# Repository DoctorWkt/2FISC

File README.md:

# FISC2: A TTL CPU with Some 16-bit Capabilities

FISC2 is a microseqenced CPU built from discrete TTL-level components.
It provides
 + recursive **F**unctions,
 + **I**ndexed addressing,
 + **S**tack operations, and
 + some instructions on 16-bit data values

as well as the usual load/store and arithmetic operations, comparisons,
branches and jumps.

The design uses 29 chips and has 8K of ROM, 336K of available RAM and a UART.

## Documentation

The overall design of the CPU is covered in
[Docs/arch_overview.md](Docs/arch_overview.md), and some details
of the hardware implementation are in 
[Docs/fisc2_implementation.md](Docs/fisc2_implementation.md).

## Implementation

At present, I have:

 + a Perl CPU simulator, [csim](csim)
 + an assembler, [cas](cas)
 + a simple compiler, [clc](clc)
 + example assembly and higher-level programs in [Examples](Examples)
 + a Verilog design in [Verilog](Verilog)
 + a final schematic in [Kicad/schematic.pdf](Kicad/schematic.pdf)

## Status of the CPU

**early-July, 2020**: Both the Perl simulator and the Verilog model work
well. I am happy with the design and I've ordered the PCBs and components.

For more detail on progress, you can read my [journal](Docs/journal.md).

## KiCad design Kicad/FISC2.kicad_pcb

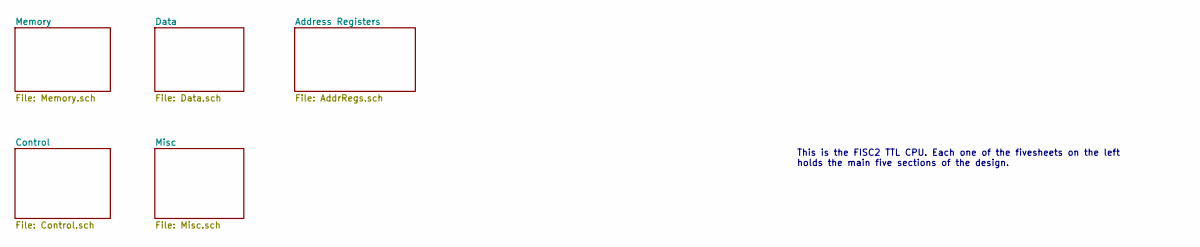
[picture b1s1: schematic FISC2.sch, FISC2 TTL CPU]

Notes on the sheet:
This is the FISC2 TTL CPU. Each one of the fivesheets on the left holds the main five sections of the design.

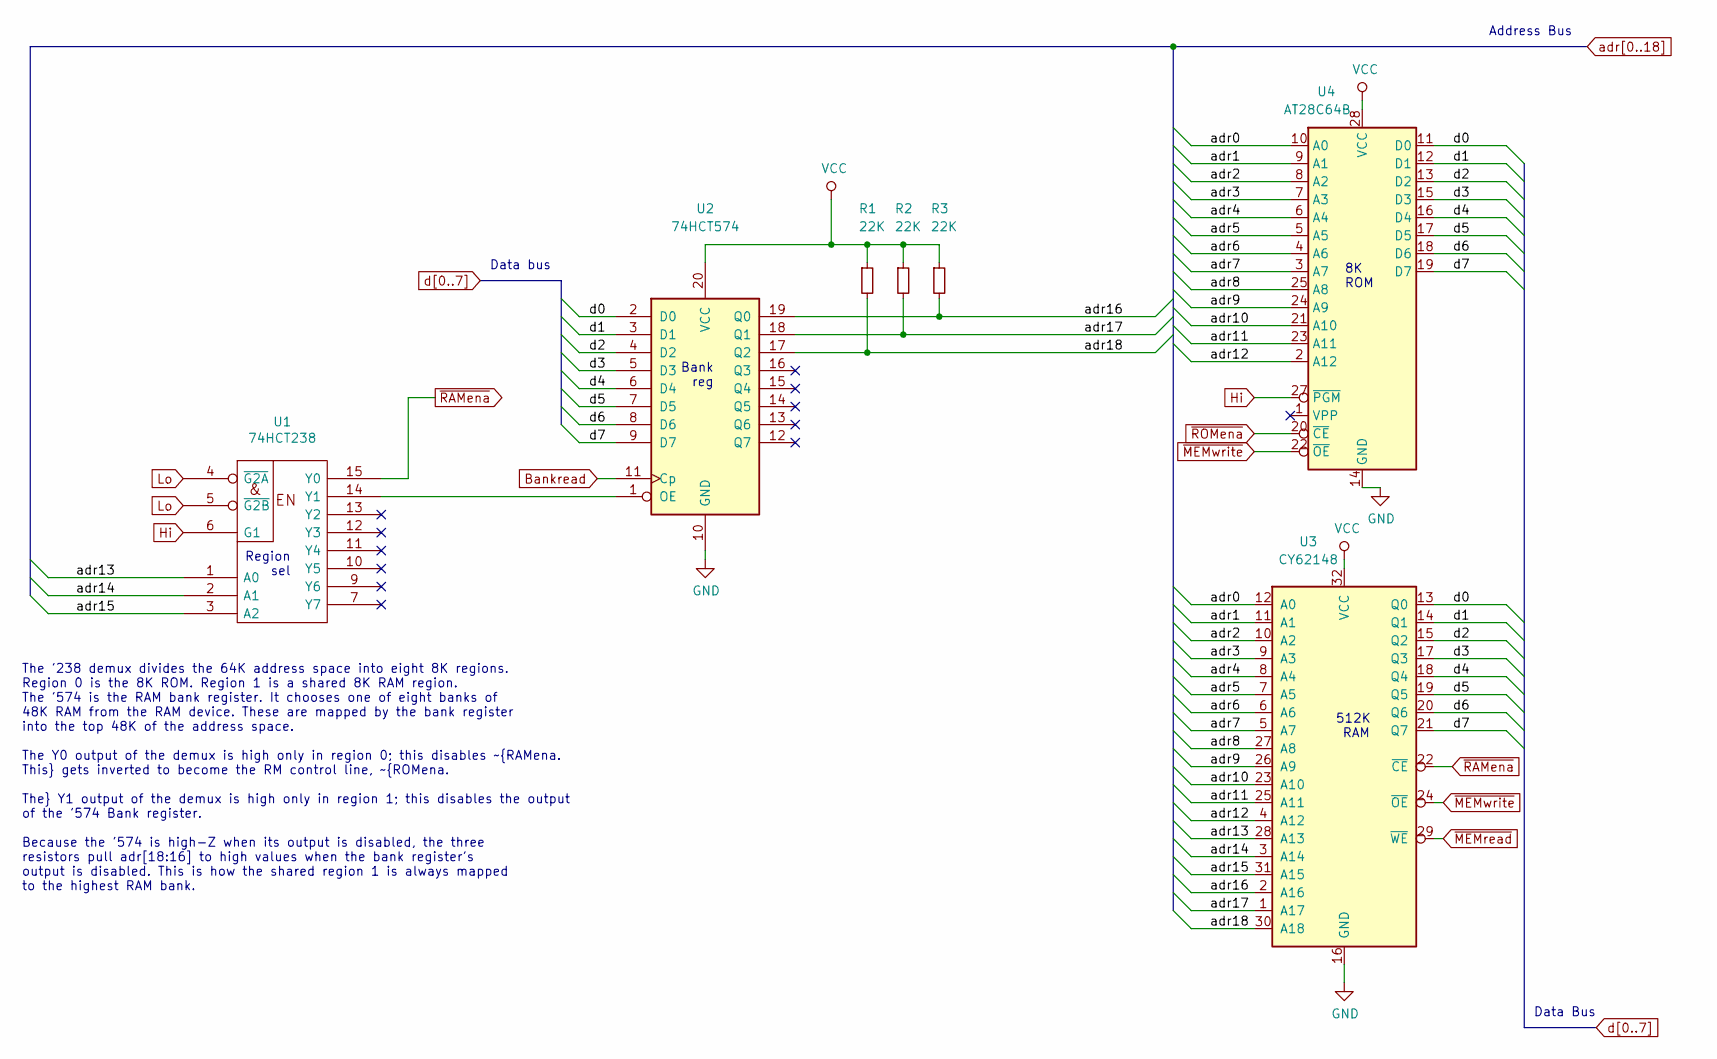
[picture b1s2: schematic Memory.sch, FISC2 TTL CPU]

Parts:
R1, R2, R3: 22K; R_0603_1608Metric_Pad1.05x0.95mm_HandSolder
U1: 74HCT238; SOIC-16_3.9x9.9mm_P1.27mm
U2: 74HCT574; SOIC-20W_7.5x12.8mm_P1.27mm
U3: CY62148; SOIC-32_11.2mm_P1.27mm
U4: AT28C64B; DIP-28_W15.24mm

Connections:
Bankread: U2.11 (Cp); also elsewhere on the board
Hi: R1.1, R2.1, R3.1, U1.6 (G1), U1.16 (VCC), U2.20 (VCC), U3.32 (VCC), U4.27 (~PGM), U4.28 (VCC); also elsewhere on the board
Lo: U1.4 (~G2A), U1.5 (~G2B), U1.8 (GND), U2.10 (GND), U3.16 (GND), U4.14 (GND); also elsewhere on the board
NNNZout: U2.8 (D6), U3.20 (Q6), U4.18 (D6); also elsewhere on the board
unnamed: U1.14 (Y1), U2.1 (OE)
NorZout: U2.6 (D4), U3.18 (Q4), U4.16 (D4); also elsewhere on the board
NotZout: U2.5 (D3), U3.17 (Q3), U4.15 (D3); also elsewhere on the board
Nout: U2.4 (D2), U3.15 (Q2), U4.13 (D2); also elsewhere on the board
ZNNout: U2.7 (D5), U3.19 (Q5), U4.17 (D5); also elsewhere on the board
Zout: U2.3 (D1), U3.14 (Q1), U4.12 (D1); also elsewhere on the board
adr0: U3.12 (A0), U4.10 (A0); also elsewhere on the board
adr1: U3.11 (A1), U4.9 (A1); also elsewhere on the board
adr2: U3.10 (A2), U4.8 (A2); also elsewhere on the board
adr3: U3.9 (A3), U4.7 (A3); also elsewhere on the board
adr4: U3.8 (A4), U4.6 (A4); also elsewhere on the board
adr5: U3.7 (A5), U4.5 (A5); also elsewhere on the board
adr6: U3.6 (A6), U4.4 (A6); also elsewhere on the board
adr7: U3.5 (A7), U4.3 (A7); also elsewhere on the board
adr8: U3.27 (A8), U4.25 (A8); also elsewhere on the board
adr9: U3.26 (A9), U4.24 (A9); also elsewhere on the board
adr10: U3.23 (A10), U4.21 (A10); also elsewhere on the board
adr11: U3.25 (A11), U4.23 (A11); also elsewhere on the board
adr12: U3.4 (A12), U4.2 (A12); also elsewhere on the board
adr13: U1.1 (A0), U3.28 (A13); also elsewhere on the board
adr14: U1.2 (A1), U3.3 (A14); also elsewhere on the board
adr15: U1.3 (A2), U3.31 (A15); also elsewhere on the board
adr16: R3.2, U2.19 (Q0), U3.2 (A16)
adr17: R2.2, U2.18 (Q1), U3.1 (A17)
adr18: R1.2, U2.17 (Q2), U3.30 (A18)
d0: U2.2 (D0), U3.13 (Q0), U4.11 (D0); also elsewhere on the board
d7: U2.9 (D7), U3.21 (Q7), U4.19 (D7); also elsewhere on the board
~MEMread: U3.29 (~WE); also elsewhere on the board
~MEMwrite: U3.24 (~OE), U4.22 (~OE); also elsewhere on the board
~RAMena: U1.15 (Y0), U3.22 (~CE); also elsewhere on the board
~ROMena: U4.20 (~CE); also elsewhere on the board

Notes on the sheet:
512K RAM
8K ROM
Address Bus
Data Bus
Data bus
The '238 demux divides the 64K address space into eight 8K regions. Region 0 is the 8K ROM. Region 1 is a shared 8K RAM region. The '574 is the RAM bank register. It chooses one of eight banks of 48K RAM from the RAM device. These are mapped by the bank register into the top 48K of the address spac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
Bank reg
Region sel

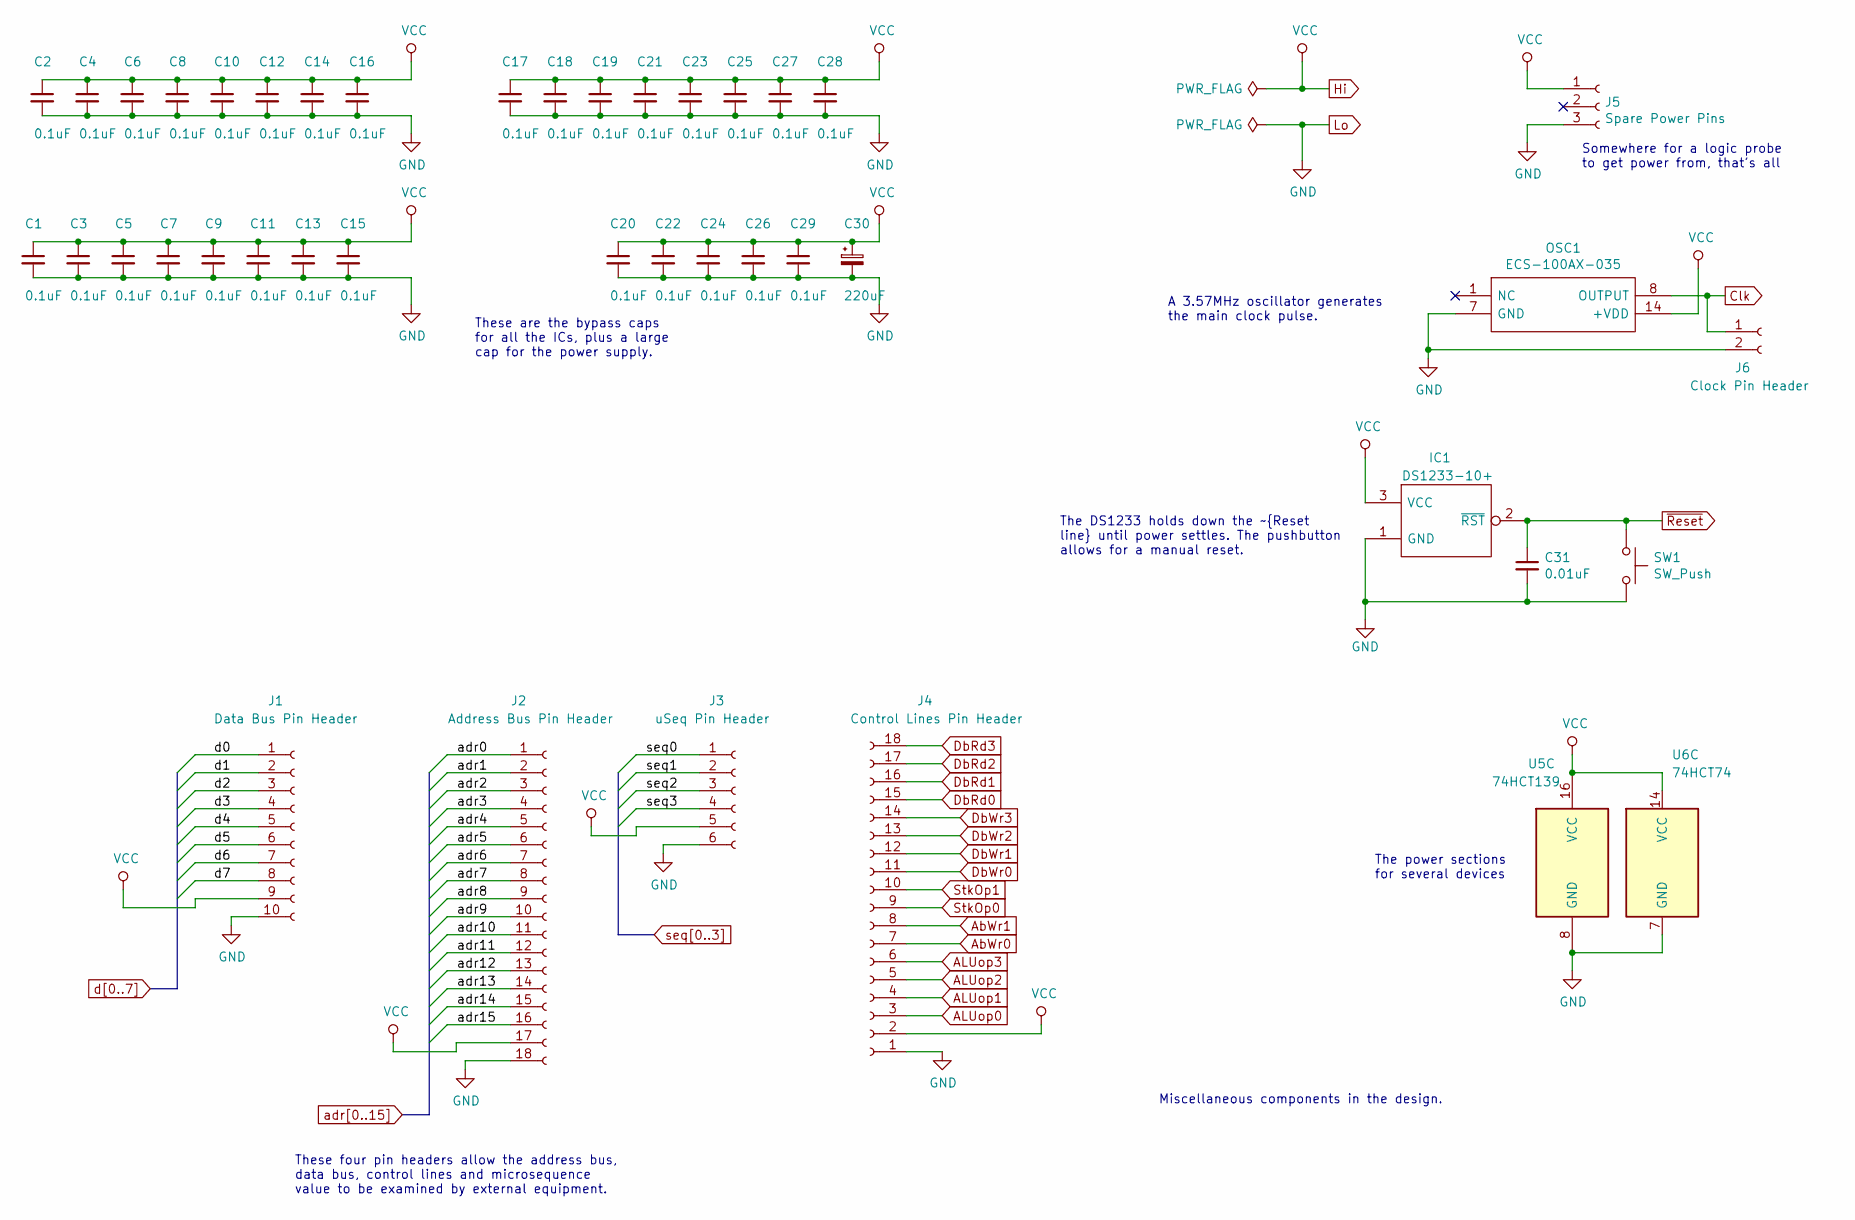
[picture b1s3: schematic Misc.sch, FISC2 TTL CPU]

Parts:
C1, C2, C3, C4, C5, C6, C7, C8, C9, C10, C11, C12, C13, C14, C15, C16, C17, C18, C19, C20, C21, C22, C23, C24, C25, C26, C27, C28, C29: 0.1uF; C_0603_1608Metric_Pad1.05x0.95mm_HandSolder
C30: 220uF; CP_Radial_D8.0mm_P5.00mm
C31: 0.01uF; C_0603_1608Metric_Pad1.05x0.95mm_HandSolder
IC1: DS1233-10+; TO-92; Manufacturer_Part_Number DS1233-10+; Mouser Part Number 700-DS1233-10
J1: Data Bus Pin Header; PinSocket_1x10_P2.54mm_Vertical
J2: Address Bus Pin Header; PinSocket_1x18_P2.54mm_Vertical
J3: uSeq Pin Header; PinSocket_1x06_P2.54mm_Vertical
J4: Control Lines Pin Header; PinSocket_1x18_P2.54mm_Vertical
J5: Spare Power Pins; PinSocket_1x03_P2.54mm_Vertical
J6: Clock Pin Header; PinSocket_1x02_P2.54mm_Vertical
OSC1: ECS-100AX-035; Oscillator_DIP-14; Manufacturer_Part_Number QX14T50B1.843200B50TT
SW1: SW_Push; Push_E-Switch_KS01Q01
U5: 74HCT139; SOIC-16_3.9x9.9mm_P1.27mm
U6: 74HCT74; SOIC-14_3.9x8.7mm_P1.27mm

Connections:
ALUop0: J4.3; also elsewhere on the board
ALUop1: J4.4; also elsewhere on the board
ALUop2: J4.5; also elsewhere on the board
ALUop3: J4.6; also elsewhere on the board
AbWr0: J4.7; also elsewhere on the board
AbWr1: J4.8; also elsewhere on the board
Clk: J6.1, OSC1.8 (OUTPUT); also elsewhere on the board
DbRd0: J4.15; also elsewhere on the board
DbRd1: J4.16; also elsewhere on the board
DbRd2: J4.17; also elsewhere on the board
DbRd3: J4.18; also elsewhere on the board
DbWr0: J4.11; also elsewhere on the board
DbWr1: J4.12; also elsewhere on the board
DbWr2: J4.13; also elsewhere on the board
DbWr3: J4.14; also elsewhere on the board
Hi: C1.1, C2.1, C3.1, C4.1, C5.1, C6.1, C7.1, C8.1, C9.1, C10.1, C11.1, C12.1, C13.1, C14.1, C15.1, C16.1, C17.1, C18.1, C19.1, C20.1, C21.1, C22.1, C23.1, C24.1, C25.1, C26.1, C27.1, C28.1, C29.1, C30.1, IC1.3 (VCC), J1.9, J2.17, J3.5, J4.2, J5.1, OSC1.14 (+VDD), U5.16 (VCC), U6.14 (VCC); also elsewhere on the board
Lo: C1.2, C2.2, C3.2, C4.2, C5.2, C6.2, C7.2, C8.2, C9.2, C10.2, C11.2, C12.2, C13.2, C14.2, C15.2, C16.2, C17.2, C18.2, C19.2, C20.2, C21.2, C22.2, C23.2, C24.2, C25.2, C26.2, C27.2, C28.2, C29.2, C30.2, C31.2, IC1.1 (GND), J1.10, J2.18, J3.6, J4.1, J5.3, J6.2, OSC1.7 (GND), SW1.2, U5.8 (GND), U6.7 (GND); also elsewhere on the board
NNNZout: J1.7; also elsewhere on the board
NorZout: J1.5; also elsewhere on the board
NotZout: J1.4; also elsewhere on the board
Nout: J1.3; also elsewhere on the board
StkOp0: J4.9; also elsewhere on the board
StkOp1: J4.10; also elsewhere on the board
ZNNout: J1.6; also elsewhere on the board
Zout: J1.2; also elsewhere on the board
adr0: J2.1; also elsewhere on the board
adr1: J2.2; also elsewhere on the board
adr2: J2.3; also elsewhere on the board
adr3: J2.4; also elsewhere on the board
adr4: J2.5; also elsewhere on the board
adr5: J2.6; also elsewhere on the board
adr6: J2.7; also elsewhere on the board
adr7: J2.8; also elsewhere on the board
adr8: J2.9; also elsewhere on the board
adr9: J2.10; also elsewhere on the board
adr10: J2.11; also elsewhere on the board
adr11: J2.12; also elsewhere on the board
adr12: J2.13; also elsewhere on the board
adr13: J2.14; also elsewhere on the board
adr14: J2.15; also elsewhere on the board
adr15: J2.16; also elsewhere on the board
d0: J1.1; also elsewhere on the board
d7: J1.8; also elsewhere on the board
seq0: J3.1; also elsewhere on the board
seq1: J3.2; also elsewhere on the board
seq2: J3.3; also elsewhere on the board
seq3: J3.4; also elsewhere on the board
~Reset: C31.1, IC1.2 (~RST), SW1.1; also elsewhere on the board

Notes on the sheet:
A 3.57MHz oscillator generates the main clock pulse.
The DS1233 holds down the ~Reset line until power settles. The pushbutton allows for a manual reset.
The power sections for several devices
These are the bypass caps for all the ICs, plus a large cap for the power supply.
These four pin headers allow the address bus, data bus, control lines and microsequence value to be examined by external equipment.
Miscellaneous components in the design.
Somewhere for a logic probe to get power from, that's all

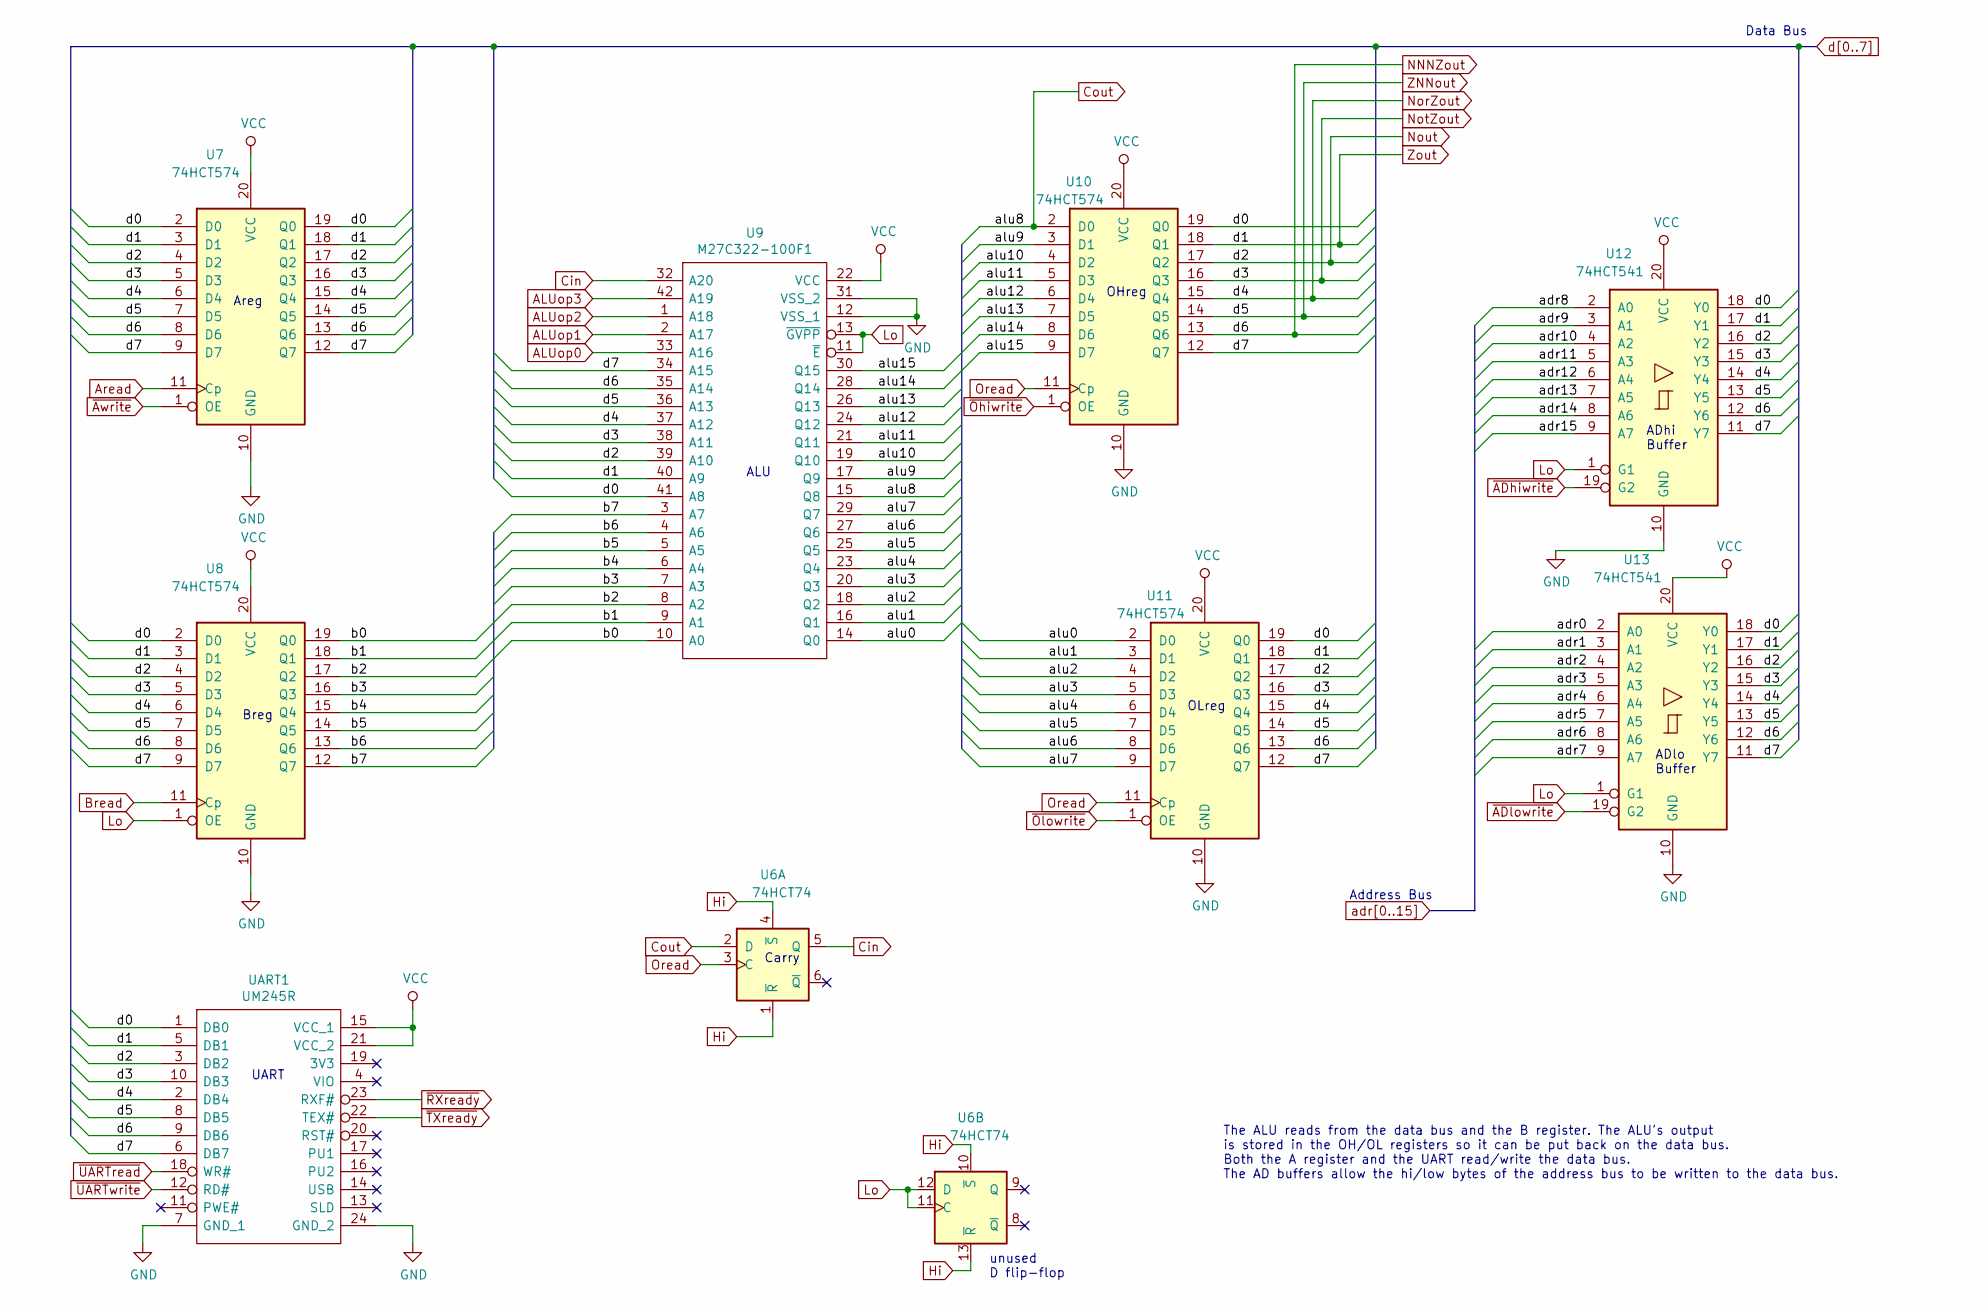
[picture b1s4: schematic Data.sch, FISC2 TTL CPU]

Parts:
U6: 74HCT74; SOIC-14_3.9x8.7mm_P1.27mm
U7, U8, U10, U11: 74HCT574; SOIC-20W_7.5x12.8mm_P1.27mm
U9: M27C322-100F1; DIP-42_W15.24mm; Manufacturer_Part_Number M27C322-100F1; Mouser Part Number 511-M27C322-10F
U12, U13: 74HCT541; SOIC-20W_7.5x12.8mm_P1.27mm
UART1: UM245R; DIP-24_W15.24mm_Socket; Manufacturer_Part_Number UM245R; Mouser Part Number 895-UM245R

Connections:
/Data/alu0: U9.14 (Q0), U11.2 (D0)
/Data/alu1: U9.16 (Q1), U11.3 (D1)
/Data/alu2: U9.18 (Q2), U11.4 (D2)
/Data/alu3: U9.20 (Q3), U11.5 (D3)
/Data/alu4: U9.23 (Q4), U11.6 (D4)
/Data/alu5: U9.25 (Q5), U11.7 (D5)
/Data/alu6: U9.27 (Q6), U11.8 (D6)
/Data/alu7: U9.29 (Q7), U11.9 (D7)
/Data/alu9: U9.17 (Q9), U10.3 (D1)
/Data/alu10: U9.19 (Q10), U10.4 (D2)
/Data/alu11: U9.21 (Q11), U10.5 (D3)
/Data/alu12: U9.24 (Q12), U10.6 (D4)
/Data/alu13: U9.26 (Q13), U10.7 (D5)
/Data/alu14: U9.28 (Q14), U10.8 (D6)
/Data/alu15: U9.30 (Q15), U10.9 (D7)
/Data/b0: U8.19 (Q0), U9.10 (A0)
/Data/b1: U8.18 (Q1), U9.9 (A1)
/Data/b2: U8.17 (Q2), U9.8 (A2)
/Data/b3: U8.16 (Q3), U9.7 (A3)
/Data/b4: U8.15 (Q4), U9.6 (A4)
/Data/b5: U8.14 (Q5), U9.5 (A5)
/Data/b6: U8.13 (Q6), U9.4 (A6)
/Data/b7: U8.12 (Q7), U9.3 (A7)
ALUop0: U9.33 (A16); also elsewhere on the board
ALUop1: U9.2 (A17); also elsewhere on the board
ALUop2: U9.1 (A18); also elsewhere on the board
ALUop3: U9.42 (A19); also elsewhere on the board
Aread: U7.11 (Cp); also elsewhere on the board
Bread: U8.11 (Cp); also elsewhere on the board
Cin: U6.5 (Q), U9.32 (A20)
Cout: U6.2 (D), U9.15 (Q8), U10.2 (D0)
Hi: U6.1 (~R), U6.4 (~S), U6.10 (~S), U6.13 (~R), U7.20 (VCC), U8.20 (VCC), U9.22 (VCC), U10.20 (VCC), U11.20 (VCC), U12.20 (VCC), U13.20 (VCC), UART1.15 (VCC_1), UART1.21 (VCC_2); also elsewhere on the board
Lo: U6.11 (C), U6.12 (D), U7.10 (GND), U8.1 (OE), U8.10 (GND), U9.11 (~E), U9.12 (VSS_1), U9.13 (~GVPP), U9.31 (VSS_2), U10.10 (GND), U11.10 (GND), U12.1 (G1), U12.10 (GND), U13.1 (G1), U13.10 (GND), UART1.7 (GND_1), UART1.24 (GND_2); also elsewhere on the board
NNNZout: U7.8 (D6), U7.13 (Q6), U8.8 (D6), U9.35 (A14), U10.13 (Q6), U11.13 (Q6), U12.12 (Y6), U13.12 (Y6), UART1.9 (DB6); also elsewhere on the board
NorZout: U7.6 (D4), U7.15 (Q4), U8.6 (D4), U9.37 (A12), U10.15 (Q4), U11.15 (Q4), U12.14 (Y4), U13.14 (Y4), UART1.2 (DB4); also elsewhere on the board
NotZout: U7.5 (D3), U7.16 (Q3), U8.5 (D3), U9.38 (A11), U10.16 (Q3), U11.16 (Q3), U12.15 (Y3), U13.15 (Y3), UART1.10 (DB3); also elsewhere on the board
Nout: U7.4 (D2), U7.17 (Q2), U8.4 (D2), U9.39 (A10), U10.17 (Q2), U11.17 (Q2), U12.16 (Y2), U13.16 (Y2), UART1.3 (DB2); also elsewhere on the board
Oread: U6.3 (C), U10.11 (Cp), U11.11 (Cp); also elsewhere on the board
ZNNout: U7.7 (D5), U7.14 (Q5), U8.7 (D5), U9.36 (A13), U10.14 (Q5), U11.14 (Q5), U12.13 (Y5), U13.13 (Y5), UART1.8 (DB5); also elsewhere on the board
Zout: U7.3 (D1), U7.18 (Q1), U8.3 (D1), U9.40 (A9), U10.18 (Q1), U11.18 (Q1), U12.17 (Y1), U13.17 (Y1), UART1.5 (DB1); also elsewhere on the board
adr0: U13.2 (A0); also elsewhere on the board
adr1: U13.3 (A1); also elsewhere on the board
adr2: U13.4 (A2); also elsewhere on the board
adr3: U13.5 (A3); also elsewhere on the board
adr4: U13.6 (A4); also elsewhere on the board
adr5: U13.7 (A5); also elsewhere on the board
adr6: U13.8 (A6); also elsewhere on the board
adr7: U13.9 (A7); also elsewhere on the board
adr8: U12.2 (A0); also elsewhere on the board
adr9: U12.3 (A1); also elsewhere on the board
adr10: U12.4 (A2); also elsewhere on the board
adr11: U12.5 (A3); also elsewhere on the board
adr12: U12.6 (A4); also elsewhere on the board
adr13: U12.7 (A5); also elsewhere on the board
adr14: U12.8 (A6); also elsewhere on the board
adr15: U12.9 (A7); also elsewhere on the board
d0: U7.2 (D0), U7.19 (Q0), U8.2 (D0), U9.41 (A8), U10.19 (Q0), U11.19 (Q0), U12.18 (Y0), U13.18 (Y0), UART1.1 (DB0); also elsewhere on the board
d7: U7.9 (D7), U7.12 (Q7), U8.9 (D7), U9.34 (A15), U10.12 (Q7), U11.12 (Q7), U12.11 (Y7), U13.11 (Y7), UART1.6 (DB7); also elsewhere on the board
~ADhiwrite: U12.19 (G2); also elsewhere on the board
~ADlowrite: U13.19 (G2); also elsewhere on the board
~Awrite: U7.1 (OE); also elsewhere on the board
~Ohiwrite: U10.1 (OE); also elsewhere on the board
~Olowrite: U11.1 (OE); also elsewhere on the board
~RXready: UART1.23 (RXF#); also elsewhere on the board
~TXready: UART1.22 (TEX#); also elsewhere on the board
~UARTread: UART1.18 (WR#); also elsewhere on the board
~UARTwrite: UART1.12 (RD#); also elsewhere on the board

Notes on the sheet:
Areg
Carry
UART
OLreg
ALU
Breg
ADhi Buffer
ADlo Buffer
Data Bus
Address Bus
The ALU reads from the data bus and the B register. The ALU's output is stored in the OH/OL registers so it can be put back on the data bus. Both the A register and the UART read/write the data bus. The AD buffers allow the hi/low bytes of the address bus to be written to the data bus.
OHreg
unused D flip-flop

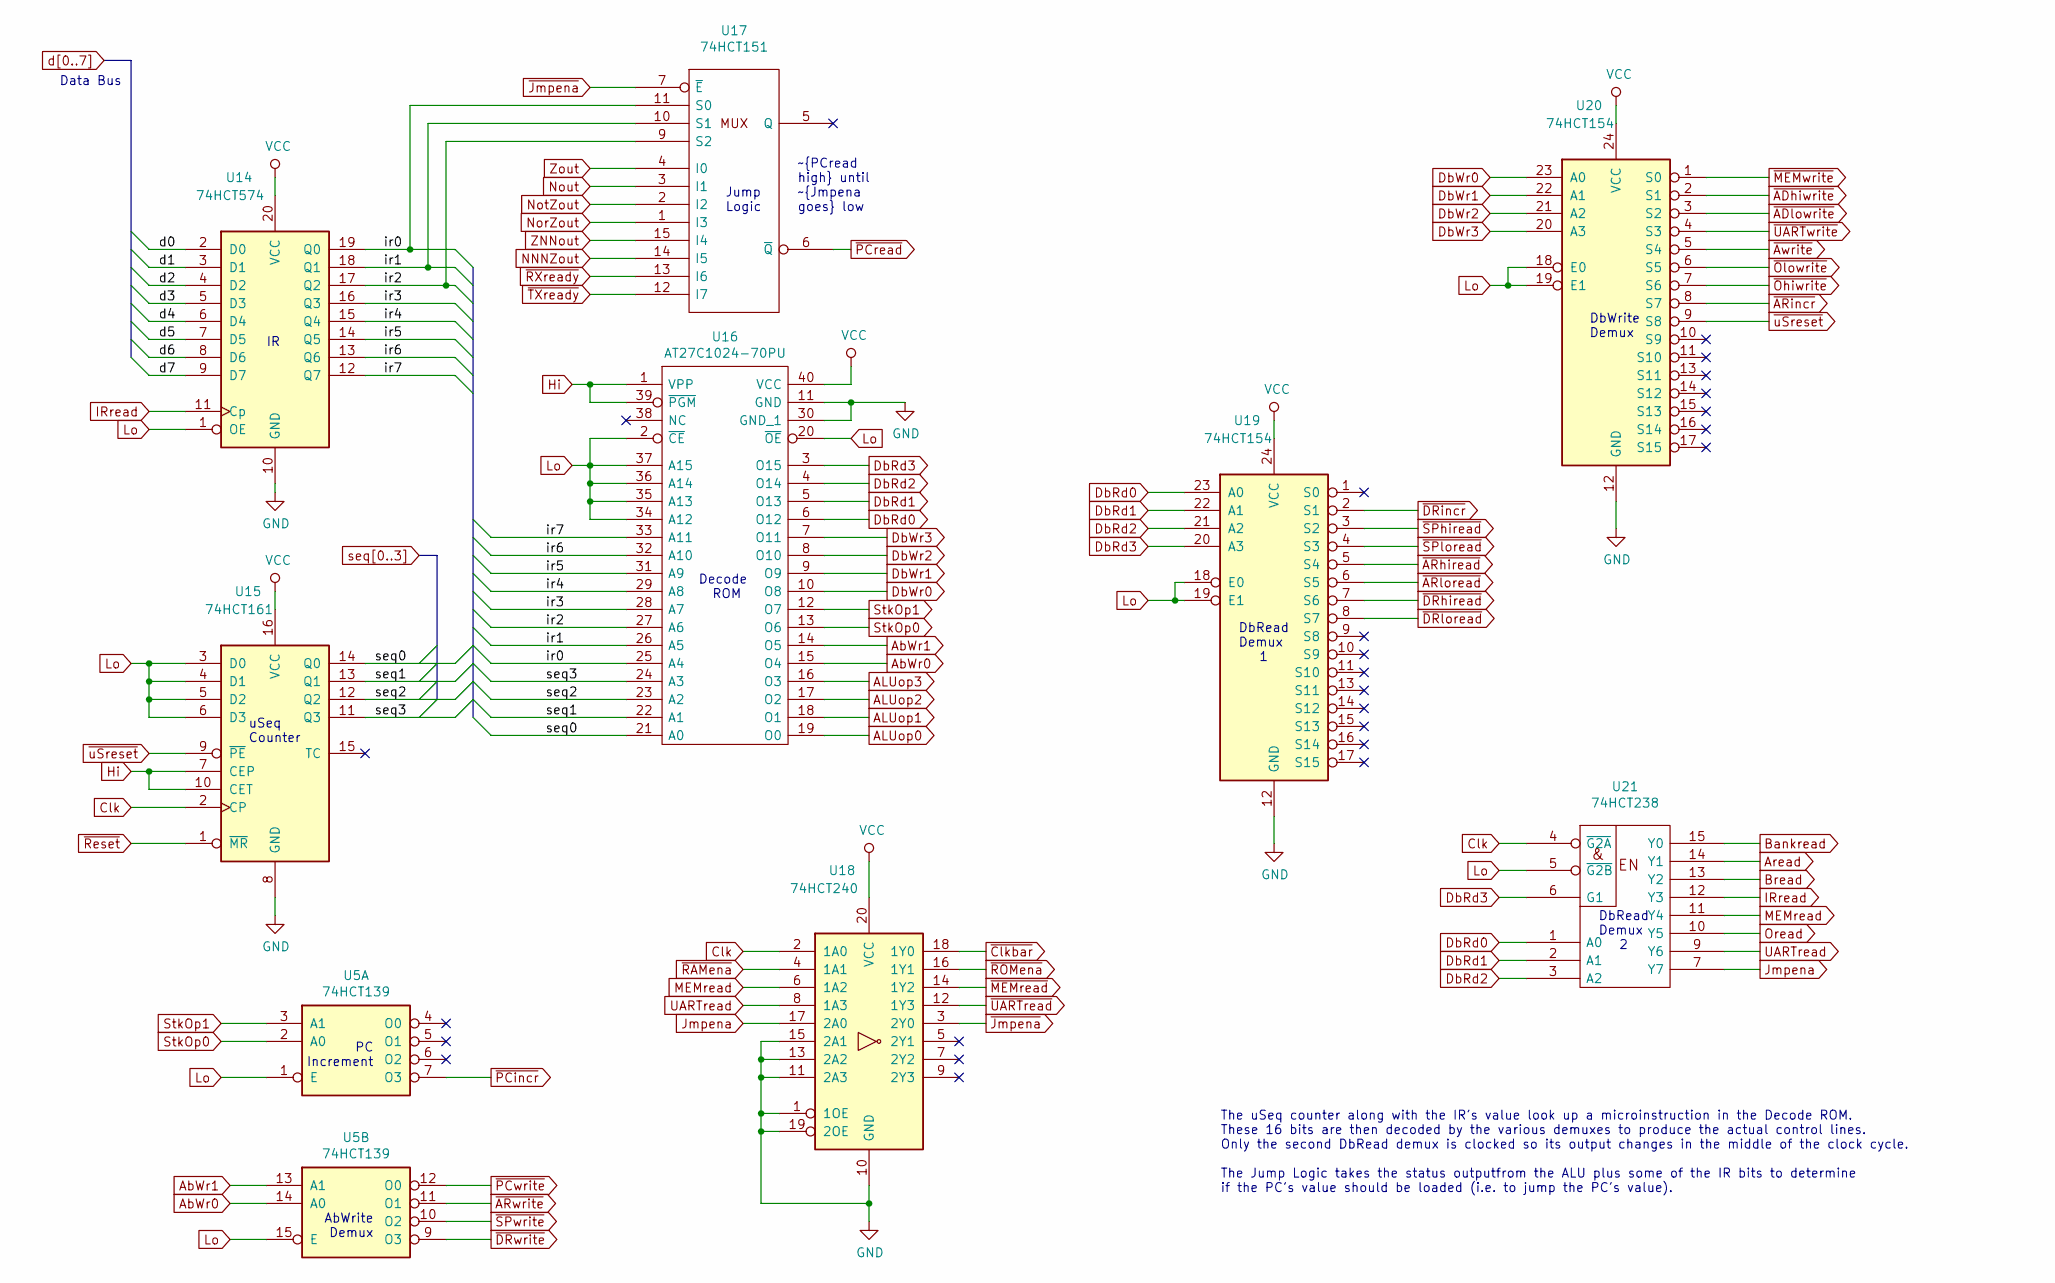
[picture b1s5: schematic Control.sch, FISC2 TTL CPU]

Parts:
U5: 74HCT139; SOIC-16_3.9x9.9mm_P1.27mm
U14: 74HCT574; SOIC-20W_7.5x12.8mm_P1.27mm
U15: 74HCT161; SOIC-16_3.9x9.9mm_P1.27mm
U16: AT27C1024-70PU; DIP-40_W15.24mm; Manufacturer_Part_Number AT27C1024-70PU; Mouser Part Number 556-AT27C102470PU
U17: 74HCT151; SOIC-16_3.9x9.9mm_P1.27mm
U18: 74HCT240; SOIC-20W_7.5x12.8mm_P1.27mm
U19, U20: 74HCT154; SOIC-24W_7.5x15.4mm_P1.27mm
U21: 74HCT238; SOIC-16_3.9x9.9mm_P1.27mm

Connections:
/Control/ir0: U14.19 (Q0), U16.25 (A4), U17.11 (S0)
/Control/ir1: U14.18 (Q1), U16.26 (A5), U17.10 (S1)
/Control/ir2: U14.17 (Q2), U16.27 (A6), U17.9 (S2)
/Control/ir3: U14.16 (Q3), U16.28 (A7)
/Control/ir4: U14.15 (Q4), U16.29 (A8)
/Control/ir5: U14.14 (Q5), U16.31 (A9)
/Control/ir6: U14.13 (Q6), U16.32 (A10)
/Control/ir7: U14.12 (Q7), U16.33 (A11)
ALUop0: U16.19 (O0); also elsewhere on the board
ALUop1: U16.18 (O1); also elsewhere on the board
ALUop2: U16.17 (O2); also elsewhere on the board
ALUop3: U16.16 (O3); also elsewhere on the board
AbWr0: U5.14 (A0), U16.15 (O4); also elsewhere on the board
AbWr1: U5.13 (A1), U16.14 (O5); also elsewhere on the board
Aread: U21.14 (Y1); also elsewhere on the board
Bankread: U21.15 (Y0); also elsewhere on the board
Bread: U21.13 (Y2); also elsewhere on the board
Clk: U15.2 (CP), U18.2 (1A0), U21.4 (~G2A); also elsewhere on the board
DbRd0: U16.6 (O12), U19.23 (A0), U21.1 (A0); also elsewhere on the board
DbRd1: U16.5 (O13), U19.22 (A1), U21.2 (A1); also elsewhere on the board
DbRd2: U16.4 (O14), U19.21 (A2), U21.3 (A2); also elsewhere on the board
DbRd3: U16.3 (O15), U19.20 (A3), U21.6 (G1); also elsewhere on the board
DbWr0: U16.10 (O8), U20.23 (A0); also elsewhere on the board
DbWr1: U16.9 (O9), U20.22 (A1); also elsewhere on the board
DbWr2: U16.8 (O10), U20.21 (A2); also elsewhere on the board
DbWr3: U16.7 (O11), U20.20 (A3); also elsewhere on the board
Hi: U14.20 (VCC), U15.7 (CEP), U15.10 (CET), U15.16 (VCC), U16.1 (VPP), U16.39 (~PGM), U16.40 (VCC), U17.16 (VCC), U18.20 (VCC), U19.24 (VCC), U20.24 (VCC), U21.16 (VCC); also elsewhere on the board
IRread: U14.11 (Cp), U21.12 (Y3)
Jmpena: U18.17 (2A0), U21.7 (Y7)
Lo: U5.1 (E), U5.15 (E), U14.1 (OE), U14.10 (GND), U15.3 (D0), U15.4 (D1), U15.5 (D2), U15.6 (D3), U15.8 (GND), U16.2 (~CE), U16.11 (GND), U16.20 (~OE), U16.30 (GND_1), U16.34 (A12), U16.35 (A13), U16.36 (A14), U16.37 (A15), U17.8 (GND), U18.1 (1OE), U18.10 (GND), U18.11 (2A3), U18.13 (2A2), U18.15 (2A1), U18.19 (2OE), U19.12 (GND), U19.18 (E0), U19.19 (E1), U20.12 (GND), U20.18 (E0), U20.19 (E1), U21.5 (~G2B), U21.8 (GND); also elsewhere on the board
MEMread: U18.6 (1A2), U21.11 (Y4)
NNNZout: U14.8 (D6), U17.14 (I5); also elsewhere on the board
NorZout: U14.6 (D4), U17.1 (I3); also elsewhere on the board
NotZout: U14.5 (D3), U17.2 (I2); also elsewhere on the board
Nout: U14.4 (D2), U17.3 (I1); also elsewhere on the board
Oread: U21.10 (Y5); also elsewhere on the board
StkOp0: U5.2 (A0), U16.13 (O6); also elsewhere on the board
StkOp1: U5.3 (A1), U16.12 (O7); also elsewhere on the board
UARTread: U18.8 (1A3), U21.9 (Y6)
ZNNout: U14.7 (D5), U17.15 (I4); also elsewhere on the board
Zout: U14.3 (D1), U17.4 (I0); also elsewhere on the board
d0: U14.2 (D0); also elsewhere on the board
d7: U14.9 (D7); also elsewhere on the board
seq0: U15.14 (Q0), U16.21 (A0); also elsewhere on the board
seq1: U15.13 (Q1), U16.22 (A1); also elsewhere on the board
seq2: U15.12 (Q2), U16.23 (A2); also elsewhere on the board
seq3: U15.11 (Q3), U16.24 (A3); also elsewhere on the board
~ADhiwrite: U20.2 (S1); also elsewhere on the board
~ADlowrite: U20.3 (S2); also elsewhere on the board
~ARhiread: U19.5 (S4); also elsewhere on the board
~ARincr: U20.8 (S7); also elsewhere on the board
~ARloread: U19.6 (S5); also elsewhere on the board
~ARwrite: U5.11 (O1); also elsewhere on the board
~Awrite: U20.5 (S4); also elsewhere on the board
~Clkbar: U18.18 (1Y0); also elsewhere on the board
~DRhiread: U19.7 (S6); also elsewhere on the board
~DRincr: U19.2 (S1); also elsewhere on the board
~DRloread: U19.8 (S7); also elsewhere on the board
~DRwrite: U5.9 (O3); also elsewhere on the board
~Jmpena: U17.7 (~E), U18.3 (2Y0)
~MEMread: U18.14 (1Y2); also elsewhere on the board
~MEMwrite: U20.1 (S0); also elsewhere on the board
~Ohiwrite: U20.7 (S6); also elsewhere on the board
~Olowrite: U20.6 (S5); also elsewhere on the board
~PCincr: U5.7 (O3); also elsewhere on the board
~PCread: U17.6 (~Q); also elsewhere on the board
~PCwrite: U5.12 (O0); also elsewhere on the board
~RAMena: U18.4 (1A1); also elsewhere on the board
~ROMena: U18.16 (1Y1); also elsewhere on the board
~RXready: U17.13 (I6); also elsewhere on the board
~Reset: U15.1 (~MR); also elsewhere on the board
~SPhiread: U19.3 (S2); also elsewhere on the board
~SPloread: U19.4 (S3); also elsewhere on the board
~SPwrite: U5.10 (O2); also elsewhere on the board
~TXready: U17.12 (I7); also elsewhere on the board
~UARTread: U18.12 (1Y3); also elsewhere on the board
~UARTwrite: U20.4 (S3); also elsewhere on the board
~uSreset: U15.9 (~PE), U20.9 (S8)

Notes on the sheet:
uSeq Counter
Decode ROM
Jump Logic
AbWrite Demux
DbRead Demux 1
Data Bus
~PCread high until ~Jmpena goes low
The uSeq counter along with the IR's value look up a microinstruction in the Decode ROM. These 16 bits are then decoded by the various demuxes to produce the actual control lines. Only the second DbRead demux is clocked so its output changes in the middle of the clock cycle. The Jump Logic takes th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
PC Increment
DbWrite Demux
DbRead Demux 2

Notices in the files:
Kicad/FISC2.kicad_pcb:
(c) 2020
